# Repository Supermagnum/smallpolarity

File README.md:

# smallpolarity, A small PCB that protects against wrong polarity.
This PCB board is 17mm in diameter, it has a four P-Channel SSM3J355R,LF channel mosfets that is capable of tolerating 20V 6A each. It should be fairly simple to solder, even that it is surface mounted. It does not conduct any electricity if subjected to the wrong polarity. It has two solder pads,the one on the DC protected side can be soldered to the top of your existing drivers spring. There is also two DC- or ground connections, I suggest a AVG 15 (1.45 mm diameter ) flexible wire for this usage. The + IN unprotected side goes to the batteries. DC OUT to the driver spring, as this is the protected side.

BOM: four P-Channel SSM3J355R

PCB :
https://oshpark.com/shared_projects/K1GudT3n

Aisler:
https://aisler.net/p/ZNMAXPIL

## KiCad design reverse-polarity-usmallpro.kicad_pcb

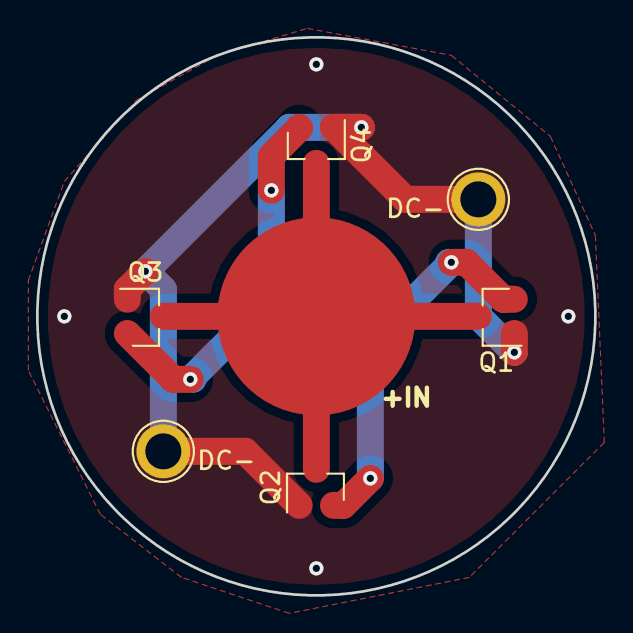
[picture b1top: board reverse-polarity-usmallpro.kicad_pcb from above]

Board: 2 copper layers, 31.0 x 31.0 mm, 8 parts (0 on the bottom side), 3 nets.

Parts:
J1: 105-1102-001; 6mmFpad-SMD
J2, J4: 105-1102-001; TestPoint_Plated_Hole_D2.0mm
J3: 105-1102-001; 6mmBpad-SMD
Q1, Q2, Q3, Q4: SSM3J355R,LF; SOT-23

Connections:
/DC+IN: J1.1, Q1.3, Q2.3, Q3.3, Q4.3
/DC+PRO: J3.1, Q1.2, Q2.2, Q3.2, Q4.2
/DC-: J2.1, J4.1, Q1.1, Q2.1, Q3.1, Q4.1

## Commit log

2020-09-05 updated gerbers
2020-09-05 updated files
